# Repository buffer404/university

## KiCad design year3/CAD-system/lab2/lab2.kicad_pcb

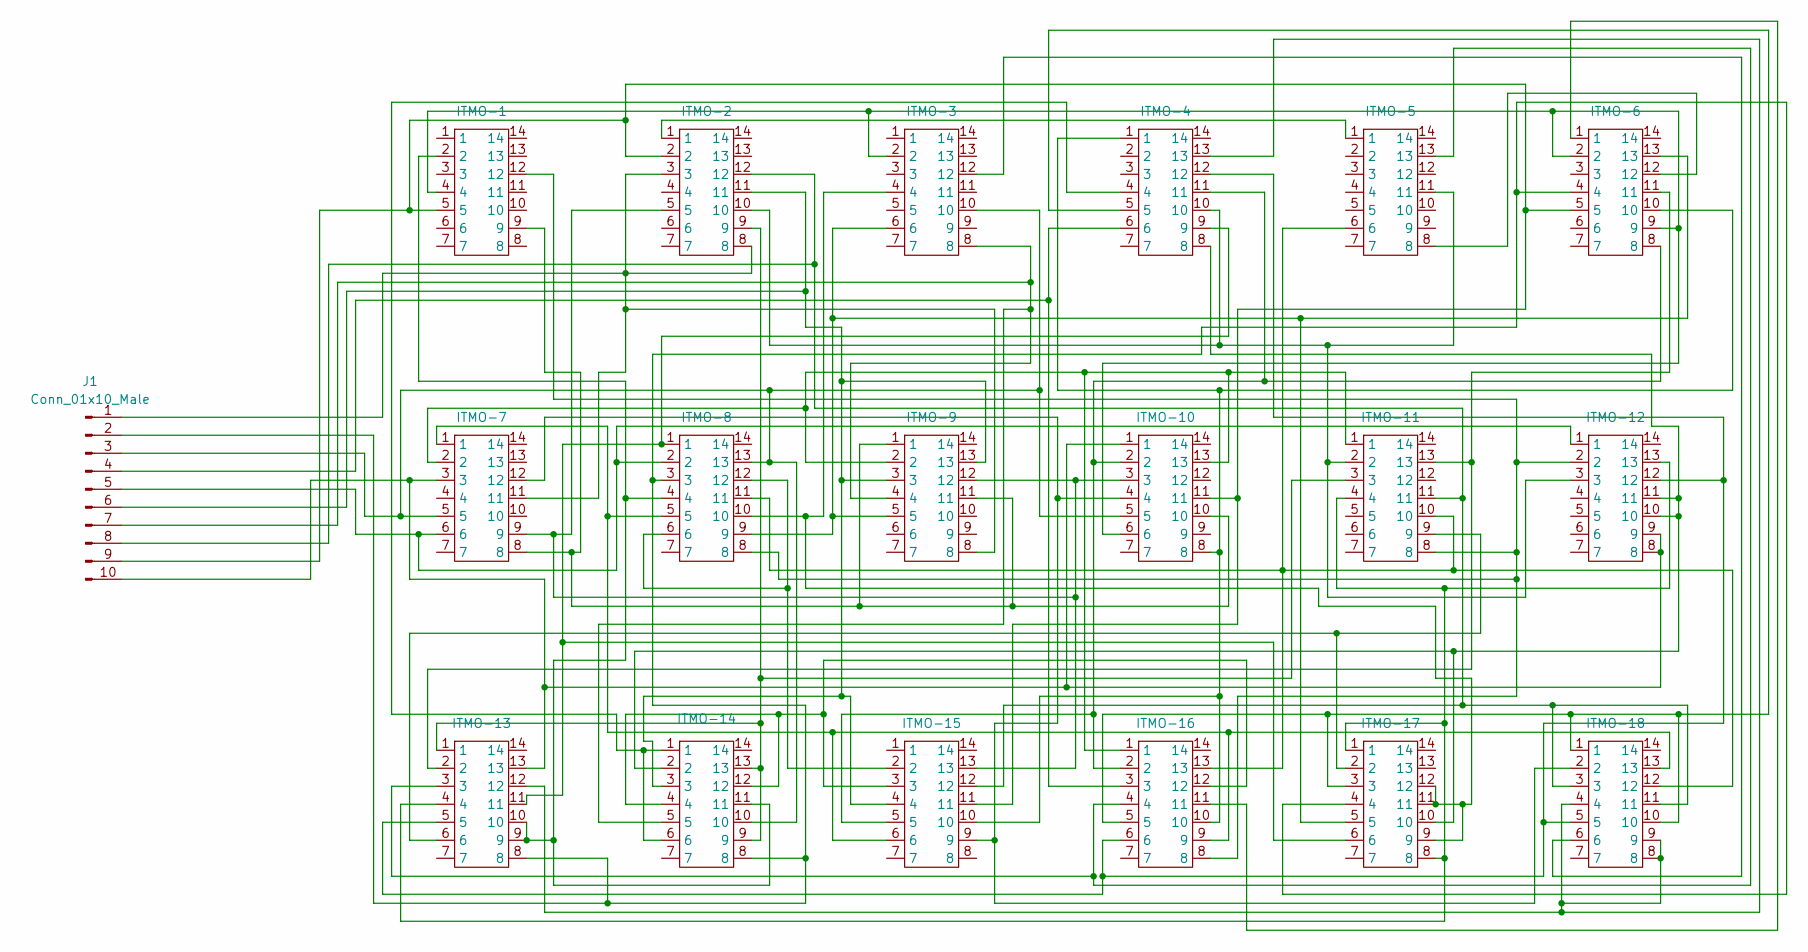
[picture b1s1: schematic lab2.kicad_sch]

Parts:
ITMO1: ITMO-1; ITMO
ITMO2: ITMO-7; ITMO
ITMO3: ITMO-13; ITMO
ITMO4: ITMO-2; ITMO
ITMO5: ITMO-8; ITMO
ITMO6: ITMO-14; ITMO
ITMO7: ITMO-3; ITMO
ITMO8: ITMO-9; ITMO
ITMO9: ITMO-15; ITMO
ITMO10: ITMO-4; ITMO
ITMO11: ITMO-10; ITMO
ITMO12: ITMO-16; ITMO
ITMO13: ITMO-5; ITMO
ITMO14: ITMO-11; ITMO
ITMO15: ITMO-17; ITMO
ITMO16: ITMO-6; ITMO
ITMO17: ITMO-12; ITMO
ITMO18: ITMO-18; ITMO
J1: Conn_01x10_Male; PinHeader_1x10_P1.00mm_Vertical

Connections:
unnamed: ITMO1.2, ITMO3.9, ITMO3.10, ITMO5.4, ITMO6.11
unnamed: ITMO1.4, ITMO7.2, ITMO11.6, ITMO16.2, ITMO16.9
unnamed: ITMO1.5, ITMO4.2, ITMO9.11, ITMO11.11, ITMO16.5, J1.9
unnamed: ITMO1.9, ITMO2.8, ITMO8.1, ITMO8.11, ITMO11.10
unnamed: ITMO1.12, ITMO5.8, ITMO12.8, ITMO14.8, ITMO17.2
unnamed: ITMO2.11, ITMO4.3, ITMO4.8, ITMO8.8, J1.1
unnamed: ITMO4.11, ITMO6.3, ITMO8.3, ITMO8.13, ITMO9.4, J1.6
unnamed: ITMO5.6, ITMO5.12, ITMO9.2
unnamed: ITMO6.5, ITMO7.8, ITMO8.4, J1.7
unnamed: ITMO9.10, ITMO10.1, ITMO11.8, ITMO12.10, ITMO16.10
unnamed: ITMO6.1, ITMO6.6, ITMO10.4
unnamed: ITMO10.5, ITMO12.5, ITMO15.3, ITMO18.1, ITMO18.10
unnamed: ITMO10.6, ITMO12.3, J1.4
unnamed: ITMO6.2, ITMO10.8, ITMO15.10, ITMO17.10, ITMO17.11
unnamed: ITMO3.11, ITMO5.1, ITMO10.9, ITMO15.6
unnamed: ITMO4.10, ITMO10.10, ITMO13.11, ITMO14.2, ITMO17.3
unnamed: ITMO9.5, ITMO10.11, ITMO11.2, ITMO12.2, ITMO16.8
unnamed: ITMO3.5, ITMO10.12, ITMO12.6, ITMO17.12, ITMO18.5
unnamed: ITMO3.12, ITMO10.13, ITMO18.4, ITMO18.8, ITMO18.9
unnamed: ITMO2.3, ITMO3.13, ITMO11.1, ITMO17.8, ITMO17.9, J1.10
unnamed: ITMO2.9, ITMO4.5, ITMO8.12, ITMO9.13, ITMO11.3
unnamed: ITMO2.12, ITMO9.9, ITMO11.4, ITMO18.2
unnamed: ITMO2.5, ITMO5.13, ITMO6.10, ITMO7.10, ITMO11.5, J1.3
unnamed: ITMO2.2, ITMO8.2, ITMO11.13, ITMO12.1, ITMO14.1
unnamed: ITMO3.3, ITMO12.4, ITMO13.13
unnamed: ITMO2.1, ITMO5.5, ITMO9.6, ITMO12.9, ITMO18.13
unnamed: ITMO12.11, ITMO16.1
unnamed: ITMO6.4, ITMO6.12, ITMO9.3, ITMO12.12
unnamed: ITMO5.11, ITMO12.13, ITMO13.6, ITMO14.10, ITMO18.12
unnamed: ITMO4.1, ITMO13.1
unnamed: ITMO13.8, ITMO16.12
unnamed: ITMO3.1, ITMO4.9, ITMO6.9, ITMO6.13, ITMO14.3
unnamed: ITMO3.4, ITMO14.4, ITMO15.1, ITMO15.8, ITMO17.13
unnamed: ITMO3.6, ITMO14.9, ITMO15.2
unnamed: ITMO4.12, ITMO9.12, ITMO14.11, ITMO18.3, ITMO18.11, J1.8
unnamed: ITMO3.2, ITMO14.13, ITMO16.11
unnamed: ITMO3.8, ITMO5.3, ITMO6.8, ITMO15.4, ITMO16.4, J1.2
unnamed: ITMO5.9, ITMO7.6, ITMO8.5, ITMO15.5, ITMO16.13
unnamed: ITMO5.10, ITMO7.4, ITMO15.9, ITMO15.11, ITMO15.12
unnamed: ITMO2.6, ITMO5.2, ITMO17.1, J1.5
unnamed: ITMO7.12, ITMO18.6

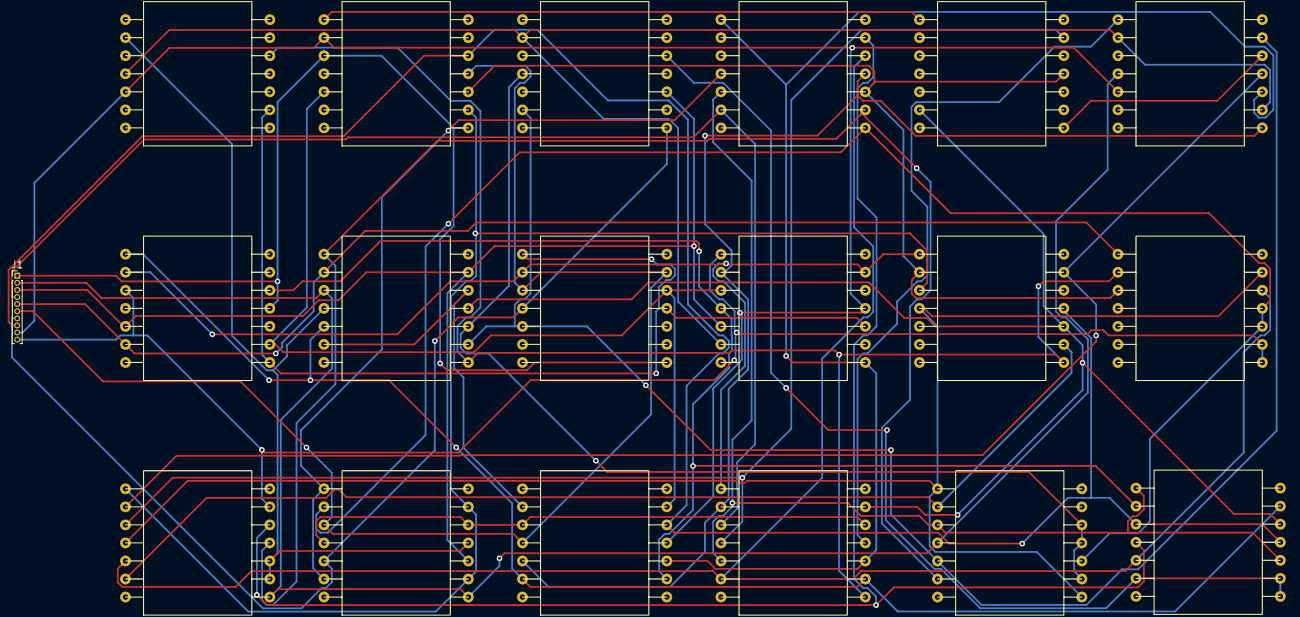
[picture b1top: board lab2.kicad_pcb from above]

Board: 2 copper layers, 19 parts (0 on the bottom side), 41 nets.

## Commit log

2022-09-11 Artificial intelligence systems 1
2022-09-11 Artificial intelligence systems report
2022-09-14 DB 1 lab init
2022-09-19 llp init
2022-09-19 sync
2022-10-14 БД 3
2022-10-25 ОС1 + АК1 + ИИ3
2022-11-08 ИИ 4
2022-11-09 БД 3й этап курсовой
2022-12-13 ОС 2
2022-12-19 ОС2 + начало АК3
2023-01-02 CSA Эссе 3
2023-01-02 trash remove
2023-01-06 ОС рубеж
2023-01-06 bugfix
2023-01-10 clear
2023-02-06 CSA 3
2023-02-06 LLP1 lab
2023-02-06 LLP upd
2023-02-19 add Digital circuitry 1
2023-03-20 Testing lab1
2023-03-20 doc add
2023-04-05 Много всего
2023-04-17 minor add
2023-04-21 minor bugfix
2023-05-23 Массовый залив 6го сема
2023-06-06 I-O System 2
2023-09-24 7sem soc1 + metr1 + security1 + design1
2023-09-24 SoC lab2 init
2023-10-04 SoC lab2 main
2023-10-04 SoC lab2 test pass
2023-11-03 local
2024-01-13 7 sem completed
